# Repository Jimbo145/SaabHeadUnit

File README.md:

# SaabHeadUnit
The goal of this project is to create an alternate head unit option for the 
## saab-control

## circuit_boards

### headunit_controls

Emulates slimmed down ICM button pcb

### headunit_hub

Integrates Ibus and LCD connections to Cat V cables for routing out of ICM

### headunit_pi4

Pi4 mounting, Lifepowered, Microphone module, power input

# Project Phases

## Phase 1 -- ICM2 Integration

Parts list
[Raspberry Pi LCD 3.5inch touchscreen 480*800 capacitive](https://www.aliexpress.us/item/3256802078662650.html)
[lifepo4wered-pi+](https://lifepo4wered.com/lifepo4wered-pi+.html)
[Can Bus Module Mcp2515](https://www.aliexpress.us/item/3256802493611620.html)

## Phase 2 -- ICM Frontend Replacement

# Acknowledgement 

[leighleighleigh](https://github.com/leighleighleigh)
[Patrick Van Oosterwijck and LiFePO4wered](https://lifepo4wered.com)
[Trionic Tuning](https://www.trionictuning.com/forum/viewtopic.php?f=46&t=8566)

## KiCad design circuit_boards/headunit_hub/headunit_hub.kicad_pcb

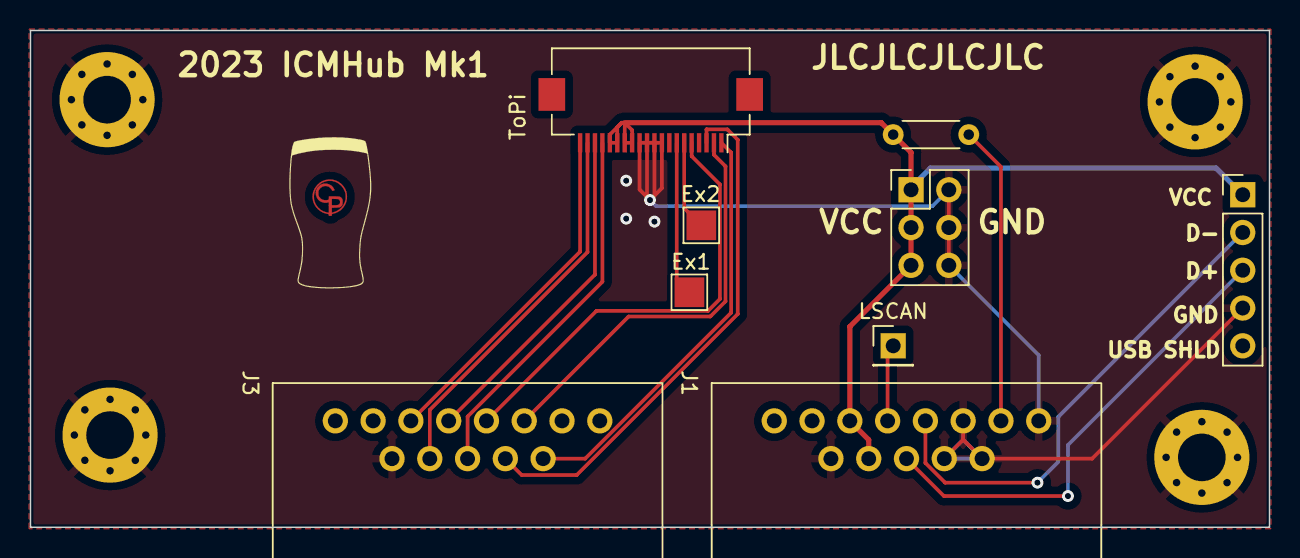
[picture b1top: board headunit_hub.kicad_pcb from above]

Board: 2 copper layers, 83.3 x 33.4 mm, 14 parts (0 on the bottom side), 16 nets.

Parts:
Ex1, Ex2: Conn_01x01_Pin; TestPoint_Pad_2.0x2.0mm
H1, H2, H4, H5: MountingHole_Pad; MountingHole_3.2mm_M3_Pad_Via
H3: Logo; CPlogo2(50)
J1, J3: 8P8C_LED_Shielded; rj45breakout
J5: USB_A; PinHeader_1x05_P2.54mm_Vertical
J6: Conn_02x03_Odd_Even; PinHeader_2x03_P2.54mm_Vertical
LSCAN: LSCAN; PinHeader_1x01_P2.54mm_Vertical
R1: R; R_Axial_DIN0204_L3.6mm_D1.6mm_P5.08mm_Horizontal
ToPi: Conn_01x20; Hirose_FH12-20S-0.5SH_1x20-1MP_P0.50mm_Horizontal

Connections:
/LSCAN: J1.6, LSCAN.1
/R_to_ActiveLED: J1.10, R1.2
AMFM_button: J3.1, ToPi.1
CD_button: J3.3, ToPi.3
Expansion_4: J3.8, ToPi.20
Expansion_5: J3.7, ToPi.19
Expansion_6: J3.6, ToPi.18
Expansion_7: J3.5, ToPi.17
GND: H1.1, H2.1, H4.1, H5.1, J1.1, J1.2, J1.3, J1.9, J1.SH, J3.SH, J5.4 (GND), J6.2, J6.4, J6.6, ToPi.9, ToPi.10, ToPi.11, ToPi.12
unnamed: Ex1.1, ToPi.7
unnamed: Ex2.1, ToPi.6
unnamed: J1.5, J5.3 (D+)
unnamed: J1.4, J5.2 (D-)
SCAN_button: J3.2, ToPi.2
Scrn_Brightness: J3.4, ToPi.5
VCC: J1.7, J1.8, J5.1 (VBUS), J6.1, J6.3, J6.5, R1.1, ToPi.13, ToPi.14, ToPi.15, ToPi.16

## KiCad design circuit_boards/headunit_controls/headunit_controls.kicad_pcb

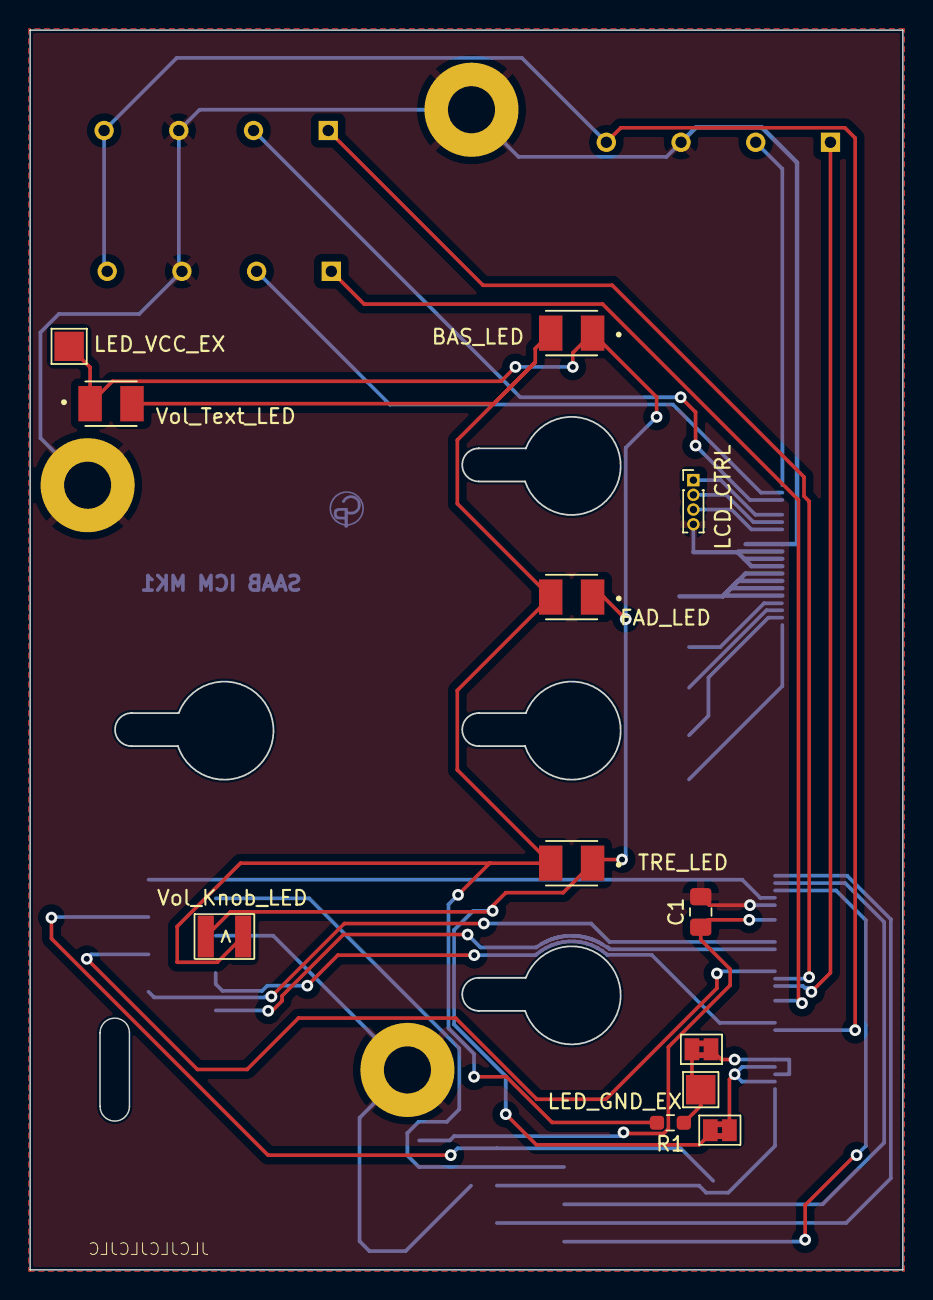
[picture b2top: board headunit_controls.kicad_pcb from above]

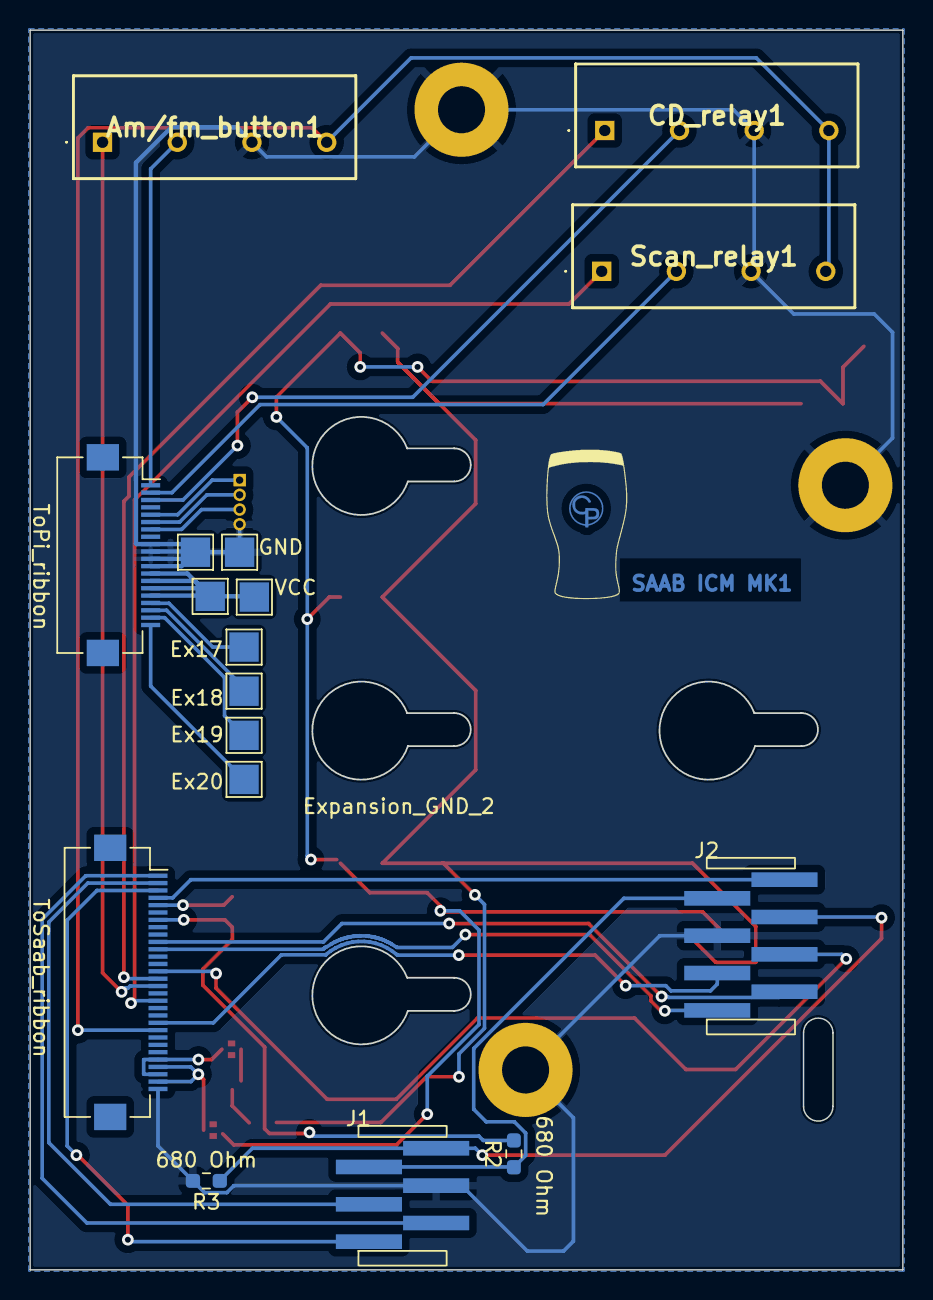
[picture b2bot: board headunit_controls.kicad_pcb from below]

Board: 2 copper layers, 59.3 x 84.3 mm, 37 parts (18 on the bottom side), 32 nets.

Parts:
Am/fm_button1: SIP-1A05; SIP1A05
BAS_LED: LED_Small; LED_OF-SMD3528WC
BTR_1, BTR_2, BTR_3: MountingHole_Pad; SaabBTR
C1: C; C_0805_2012Metric_Pad1.18x1.45mm_HandSolder
CD_relay1: SIP-1A05; SIP1A05
Ex17, Ex18, Ex19, Ex20: Conn_01x01_Pin; TestPoint_Pad_2.0x2.0mm
Expansion_GND_2: Conn_01x01_Pin; TestPoint_Pad_2.0x2.0mm
Expansion_VCC_2: Conn_01x01_Pin; TestPoint_Pad_2.0x2.0mm
FAD_LED: LED_Small; LED_OF-SMD3528WC
GND: Conn_01x01_Pin; TestPoint_Pad_2.0x2.0mm
J1: Conn_01x06; SaabConnector_6
J2: Conn_01x08; SaabConnector_8
JP1, JP2: SolderJumper_2_Bridged; SolderJumper-2_P1.3mm_Bridged2Bar_Pad1.0x1.5mm
LCD_CTRL: Conn_01x04_Pin; PinHeader_1x04_P1.00mm_Vertical
LED_GND_EX: Conn_01x01_Pin; TestPoint_Pad_2.0x2.0mm
LED_VCC_EX: Conn_01x01_Pin; TestPoint_Pad_2.0x2.0mm
M3_1, M3_2, M3_3: MountingHole_Pad; MountingHole_3.2mm_M3_Pad
R1: R; R_0603_1608Metric_Pad0.98x0.95mm_HandSolder
R2, R3: 680 Ohm; R_0603_1608Metric_Pad0.98x0.95mm_HandSolder
Ref**: Val**; CPlogo2(50)
Scan_relay1: SIP-1A05; SIP1A05
TRE_LED: LED_Small; LED_OF-SMD3528WC
ToPi_ribbon: Conn_01x20; Hirose_FH12-20S-0.5SH_1x20-1MP_P0.50mm_Horizontal
ToSaab_ribbon: Conn_01x30; Hirose_FH12-30S-0.5SH_1x30-1MP_P0.50mm_Horizontal
VCC: Conn_01x01_Pin; TestPoint_Pad_2.0x2.0mm
VOL_1: MountingHole_Pad; SaabBTR
Vol_Knob_LED: LED_Small; Songxin_1210_side
Vol_Text_LED: LED_Small; LED_OF-SMD3528WC

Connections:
15: CD_relay1.1 (Contact_A), ToSaab_ribbon.15
16: Am/fm_button1.1 (Contact_A), ToSaab_ribbon.16
18: Scan_relay1.1 (Contact_A), ToSaab_ribbon.18
22: Am/fm_button1.4 (Contact_B), CD_relay1.4 (Contact_B), Scan_relay1.4 (Contact_B), ToSaab_ribbon.22
/SCREEN_CLK: LCD_CTRL.2, ToPi_ribbon.6
/SCREEN_DIO: LCD_CTRL.3, ToPi_ribbon.7
/SCREEN_RST: LCD_CTRL.1, ToPi_ribbon.5
AMFM_button: Am/fm_button1.2 (Coil_A), ToPi_ribbon.1
BAS: J1.3, ToSaab_ribbon.2
BTFR_BALL_CON: C1.1, R2.2, ToSaab_ribbon.7
Bal_Center: J2.8, ToSaab_ribbon.4
CD_button: CD_relay1.2 (Coil_A), ToPi_ribbon.3
FAD: J1.2, ToSaab_ribbon.1
GND: Am/fm_button1.3 (Coil_B), C1.2, CD_relay1.3 (Coil_B), Expansion_GND_2.1, GND.1, J1.4, J2.5, LCD_CTRL.4, M3_1.1, M3_2.1, M3_3.1, R3.2, Scan_relay1.3 (Coil_B), ToPi_ribbon.9, ToPi_ribbon.10, ToPi_ribbon.11, ToPi_ribbon.12, ToSaab_ribbon.5, ToSaab_ribbon.9, ToSaab_ribbon.30
LED_Feed: JP1.1 (A), ToSaab_ribbon.26, ToSaab_ribbon.28
LED_GND: JP2.2 (B), ToSaab_ribbon.27, ToSaab_ribbon.29
unnamed: BAS_LED.2 (A), FAD_LED.2 (A), R1.2, TRE_LED.2 (A), Vol_Knob_LED.2 (A), Vol_Text_LED.2 (A)
unnamed: BAS_LED.1 (K), FAD_LED.1 (K), JP2.1 (A), LED_VCC_EX.1, TRE_LED.1 (K), Vol_Knob_LED.1 (K), Vol_Text_LED.1 (K)
unnamed: Ex17.1, ToPi_ribbon.17
unnamed: Ex18.1, ToPi_ribbon.18
unnamed: Ex19.1, ToPi_ribbon.19
unnamed: Ex20.1, ToPi_ribbon.20
unnamed: JP1.2 (B), LED_GND_EX.1, R1.1
unnamed: J1.5, J2.7, R2.1
unnamed: J1.6, J2.6, R3.1
unnamed: J2.4, ToSaab_ribbon.14
SCAN_button: Scan_relay1.2 (Coil_A), ToPi_ribbon.2
TRE: J1.1, ToSaab_ribbon.3
VCC: Expansion_VCC_2.1, ToPi_ribbon.13, ToPi_ribbon.14, ToPi_ribbon.15, ToPi_ribbon.16, VCC.1
Vol_buttonB: J2.3, ToSaab_ribbon.21
Vol_encA: J2.2, ToSaab_ribbon.10
Vol_encB: J2.1, ToSaab_ribbon.11

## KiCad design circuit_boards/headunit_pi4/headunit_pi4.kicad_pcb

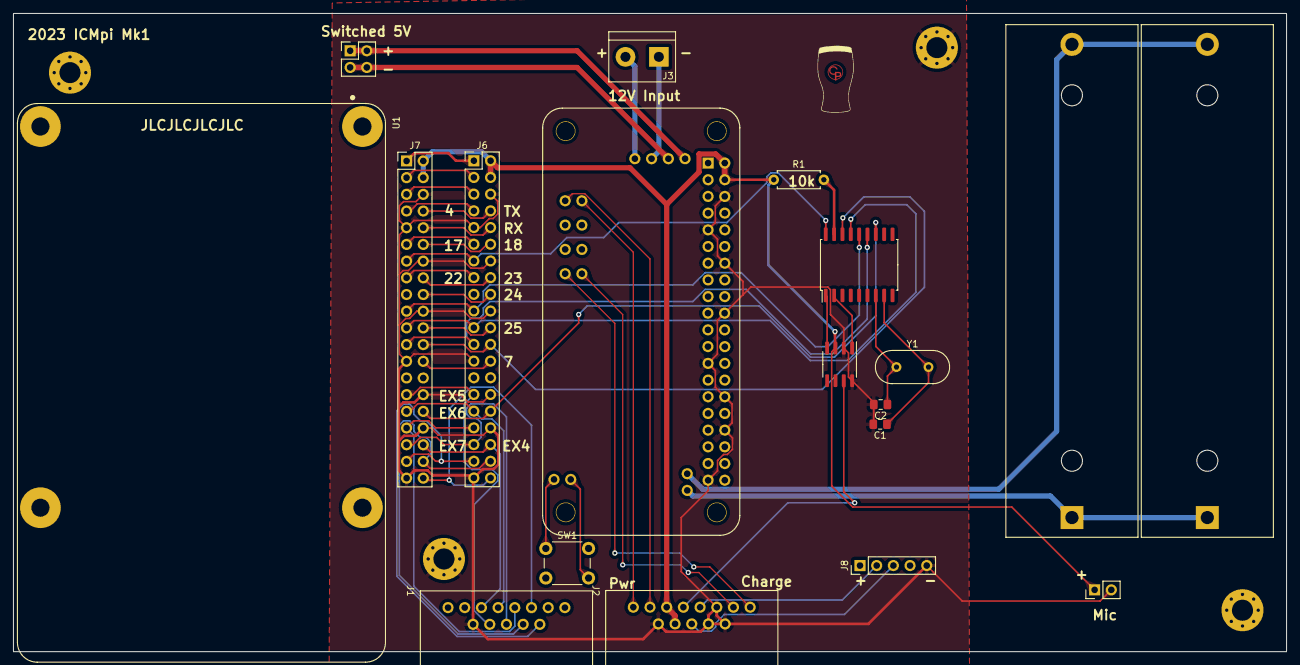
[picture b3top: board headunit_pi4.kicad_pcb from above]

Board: 2 copper layers, 193.7 x 97.1 mm, 24 parts (0 on the bottom side), 50 nets.

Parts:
BT1, BT2: Battery_Cell; BatteryHolder_MPD_BH-18650-PC2
C1, C2: 22p; C_0805_2012Metric_Pad1.18x1.45mm_HandSolder
H1, H2, H3, H4: MountingHole_Pad; MountingHole_3.2mm_M3_Pad_Via
H5: MountingHole; CPlogo2(50)
J1, J2: 8P8C_LED_Shielded; rj45breakout
J3: Screw_Terminal_01x02; TerminalBlock_bornier-2_P5.08mm
J4: Conn_01x02; PinHeader_1x02_P2.54mm_Vertical
J5: Conn_02x02_Counter_Clockwise; PinHeader_2x02_P2.54mm_Vertical
J6, J7: Conn_02x20_Odd_Even; PinHeader_2x20_P2.54mm_Vertical
J8: USB_B_Mini; PinHeader_1x05_P2.54mm_Vertical
R1: 10k; R_Axial_DIN0207_L6.3mm_D2.5mm_P7.62mm_Horizontal
SW1: SW_Push; SW_PUSH_6mm
U1: RASPBERRY_PI_4B_4GB; MODULE_RASPBERRY_PI_4B_4GB_NOPIN
U2: TJA1051T; SOIC-8_3.9x4.9mm_P1.27mm
U3: MCP2515-xSO; SOIC-18W_7.5x11.6mm_P1.27mm
U4: LiFoPower
Y1: 8Mhz; Crystal_HC49-U_Vertical

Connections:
+3.3V: J6.1, J7.1
AMFM_button: J1.1, J6.37, J7.37
CAN_INT: J6.32, J7.32, U3.12 (~INT)
CD_button: J1.3, J6.38, J7.38
ChargeLED+: J2.10, U4.Cled+ (ChargeLED+)
ChargeLED-: J2.9, U4.Cled- (ChargeLED-)
Expansion_4: J1.8, J6.36, J7.36
Expansion_5: J1.7, J6.29, J7.29
Expansion_6: J1.6, J6.31, J7.31
Expansion_7: J1.5, J6.35, J7.35
GND: C1.2, C2.2, H1.1, H2.1, H3.1, H4.1, J1.SH, J2.1, J2.2, J2.3, J2.SH, J4.2, J6.6, J6.9, J6.14, J6.20, J6.25, J6.30, J6.34, J6.39, J7.6, J7.9, J7.14, J7.20, J7.25, J7.30, J7.34, J7.39, J8.5 (GND), U2.2 (GND), U2.8 (S), U4.6 (GND), U4.9 (GND), U4.14 (GND), U4.20 (GND), U4.25 (GND), U4.30 (GND), U4.34 (GND), U4.39 (GND)
GPIO4: J6.7, J7.7
GPIO7: J6.26, J7.26
GPIO17: J6.11, J7.11
GPIO18: J6.12, J7.12
GPIO22: J6.15, J7.15
GPIO23: J6.16, J7.16
GPIO24: J6.18, J7.18
GPIO25: J6.22, J7.22
LSCAN: J2.6, U2.7 (CANH)
MCP_PWR: J6.13, J7.13, U3.18 (VDD)
unnamed: BT1.1 (+), BT2.1 (+), U4.B+ (Bat+)
unnamed: BT1.2 (-), BT2.2 (-), U4.B- (Bat-)
unnamed: J3.1, U4.Vcar- (12VGND)
unnamed: J3.2, U4.Vcar+ (12V+)
unnamed: J5.1, J5.2, U4.Vout+
unnamed: J5.3, J5.4, U4.Vout-
unnamed: J2.5, J8.3 (D+)
unnamed: J2.4, J8.2 (D-)
unnamed: U1.S1 (SHIELD), U1.S2 (SHIELD), U1.S3 (SHIELD), U1.S4 (SHIELD)
unnamed: U2.4 (RXD), U3.1 (TXCAN)
unnamed: U2.1 (TXD), U3.2 (RXCAN)
unnamed: C1.1, U3.8 (OSC1), Y1.2
unnamed: C2.1, U3.7 (OSC2), Y1.1
unnamed: R1.2, U3.17 (~RESET)
unnamed: SW1.2, U4.btn+ (BTN+)
unnamed: SW1.1, U4.btn- (BTN-)
PwrLED+: J2.12, U4.Pled+ (PowerLED+)
PwrLED-: J2.11, U4.Pled- (PowerLED-)
RX0: J6.10, J7.10
SCAN_button: J1.2, J6.40, J7.40
SCL1: J6.5, J7.5, U4.5 (SCL)
SDA1: J6.3, J7.3, U4.3 (SDA)
SPI0_CE0: J6.24, J7.24, U3.16 (~CS)
SPI0_MISO: J6.21, J7.21, U3.15 (SO)
SPI0_MOSI: J6.19, J7.19, U3.14 (SI)
SPI0_SCLK: J6.23, J7.23, U3.13 (SCK)
Scrn_Brightness: J1.4, J6.33, J7.33
TX0: J6.8, J7.8, U4.8 (TX0)
VCC: J2.7, J2.8, J4.1, J6.2, J6.4, J7.2, J7.4, R1.1, U2.3 (VCC), U4.2 (VCC), U4.4 (VCC)

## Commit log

2021-05-27 Initial commit native pigpio control
2021-05-27 Update Git Ignore
2021-05-30 Somewhat working SDL package
2023-01-27 Initial commit of saab-control python scripts
2023-01-30 Add installation script and service
2023-02-11 changes to name structure and python location
2023-02-15 Update file paths
2023-03-05 Update file paths add turn signal logic
2023-03-06 Add pyzmq import
2023-03-07 Change Service script location
2023-03-07 Change Service script location (#2)
2023-03-13 Remove gitpython
2023-03-13 Dev (#3)
    * Change Service script location
    * Remove gitpython
    ---------
2023-03-14 Attempt to move Fog light on and aux change to updater.
2023-03-14 Dev (#4)
    * Change Service script location
    * Remove gitpython
    * Attempt to move Fog light on and aux change to updater.
    ---------
2023-03-14 Change Updater to run in a standalone service
2023-03-14 Dev (#5)
    * Change Service script location
    * Remove gitpython
    * Attempt to move Fog light on and aux change to updater.
    * Change Updater to run in a standalone service
    * Change Updater to run in a standalone service
    ---------
2023-03-14 Modify service files so they point to right path and are executed in order
2023-03-14 Dev (#6)
    * Change Service script location
    * Remove gitpython
    * Attempt to move Fog light on and aux change to updater.
    * Change Updater to run in a standalone service
    * Change Updater to run in a standalone service
    * Modify service files so they point to right path and are executed in order
2023-03-14 Dev (#7)
    * Change Service script location
    * Remove gitpython
    * Attempt to move Fog light on and aux change to updater.
    * Change Updater to run in a standalone service
    * Change Updater to run in a standalone service
    * Modify service files so they point to right path and are executed in order
2023-03-14 modify install.sh to work if already installed. Move After key in saab.service
2023-03-14 Dev (#8)
    * Change Service script location
    * Remove gitpython
    * Attempt to move Fog light on and aux change to updater.
    * Change Updater to run in a standalone service
    * Change Updater to run in a standalone service
    * Modify service files so they point to right path and are executed in order
2023-03-14 modify radio change messages, move foglight on back to saabCan.py
2023-03-14 Dev (#9)
    * Change Service script location
    * Remove gitpython
    * Attempt to move Fog light on and aux change to updater.
    * Change Updater to run in a standalone service
    * Change Updater to run in a standalone service
    * Modify service files so they point to right path and are executed in order
2023-03-15 Change copy command to bash
2023-03-15 Dev (#10)
    * Change Service script location
    * Remove gitpython
    * Attempt to move Fog light on and aux change to updater.
    * Change Updater to run in a standalone service
    * Change Updater to run in a standalone service
    * Modify service files so they point to right path and are executed in order
2023-03-20 remove attempt at automatic radio change. change back to get pull
2023-03-20 Dev (#11)
    * Change Service script location
    * Remove gitpython
    * Attempt to move Fog light on and aux change to updater.
    * Change Updater to run in a standalone service
    * Change Updater to run in a standalone service
    * Modify service files so they point to right path and are executed in order
2023-03-21 Update to updater to only update when updates are required
2023-03-21 Update to updater to only update when updates are required (#12)
2023-03-28 import os and remove unnecessary requirements for saab.service
2023-03-28 Updater refresh (#13)
    * Update to updater to only update when updates are required
    * import os and remove unnecessary requirements for saab.service
    ---------
2023-03-31 add api (currently commented out). add journalctl logging add automatic source changing
2023-03-31 Dev (#14)
    * Change Service script location
    * Remove gitpython
    * Attempt to move Fog light on and aux change to updater.
    * Change Updater to run in a standalone service
    * Change Updater to run in a standalone service
    * Modify service files so they point to right path and are executed in order
2023-04-05 Add Async to get_battery_status and extend install.sh
2023-04-06 Dev (#15)
    * Change Service script location
    * Remove gitpython
    * Attempt to move Fog light on and aux change to updater.
    * Change Updater to run in a standalone service
    * Change Updater to run in a standalone service
    * Modify service files so they point to right path and are executed in order
2023-04-10 add requirements.txt change systemd journal handling
2023-04-10 Dev (#16)
    * Change Service script location
    * Remove gitpython
    * Attempt to move Fog light on and aux change to updater.
    * Change Updater to run in a standalone service
    * Change Updater to run in a standalone service
    * Modify service files so they point to right path and are executed in order
2023-04-12 Update updater
2023-04-12 Dev (#17)
    * Change Service script location
    * Remove gitpython
    * Attempt to move Fog light on and aux change to updater.
    * Change Updater to run in a standalone service
    * Change Updater to run in a standalone service
    * Modify service files so they point to right path and are executed in order
2023-04-12 Start updater sooner, and stop if an update is necessary.
2023-04-12 Start updater sooner, and stop if an update is necessary. (#18)
2023-04-14 Bug Fix: use systemd-python rather than systemd
2023-04-14 Bug Fix: use systemd-python rather than systemd (#19)
2023-04-14 Bug Fix: add back can configuration, add await to copy_files
2023-04-14 Bug Fix: add back can configuration, add await to copy_files (#20)
2023-04-14 Create python-app.yml (#21)
2023-04-15 Fix saab.service script path. Add absolute path to requirements.txt for installer
2023-04-15 Fix saab.service script path. Add absolute path to requirements.txt for installer (#22)
2023-04-15 logger changes, call ip link up as sudo
2023-04-15 logger changes, call ip link up as sudo (#23)
2023-04-15 fix duplicate bracket
2023-04-15 fix duplicate bracket (#24)
2023-04-15 Change saab_update to graphical.target
2023-04-15 Change saab_update to graphical.target (#25)
2023-04-16 logging changes, fix message not sending until receive
2023-04-16 Dev (#26)
    * Change saab_update to graphical.target
    * logging changes, fix message not sending until receive
    ---------
2023-04-18 Feature: Add Auto-restart to saab.service
2023-04-18 Feature: Add Auto-restart to saab.service (#27)
2023-04-22 Add wait condition for pynput to prevent saabCan from failing if Xorg is not yet available
2023-04-22 Add wait condition for pynput to prevent saabCan from failing if Xorg is not yet available (#28)
2023-04-22 Fix source change button send, change log levels
2023-04-22 Fix source change button send, change log levels (#29)
2023-04-22 Fix source change button send, change log levels (#30)
2023-04-23 Fix update check, again change logging
2023-04-23 Fix update check, again change logging (#31)
2023-04-24 Bug fix: increase source change delay Feature: Additional logging support
2023-04-24 Bug fix: increase source change delay (#32)
    Feature: Additional logging support
2023-04-25 Cleanup repo and add documentation
2023-04-25 Cleanup repo and add documentation (#33)
2023-04-25 Feature: Add Additional Can Message Support
2023-04-25 Feature: Add Additional Can Message Support (#34)
2023-04-27 Add preliminary support for more can ids. Fix NXT button support
2023-04-28 Add preliminary support for more can ids.
2023-04-28 Adjust update
2023-04-28 Adjust update (#35)
2023-04-28 BugFix: Turn signal global variables not defined until 290 message received Feature: Added 0x143 and 0x144 canid support (windshield wipers) Change: Change 0x180 and 0x183 (Parking sensor) log messag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
2023-05-01 BugFix: Turn signal global variables not defined until 290 message received (#36)
    Feature: Added 0x143 and 0x144 canid support (windshield wipers)
    Change: Change 0x180 and 0x183 (Parking sensor) log message level
2023-05-03 Bug Fix: Turn signal handle direction Bug Fix: Fix Right turn signal timer Feature: Added Update Rev to update file
2023-05-03 Bug Fix: Turn signal handle direction (#37)
    Bug Fix: Fix Right turn signal timer
    Feature: Added Update Rev to update file
2024-02-10 Modified Kicad Files
2024-02-10 BugFix: Turn signal euro flash always active
2024-02-10 Dev (#38)
    * BugFix: Turn signal global variables not defined until 290 message received
    Feature: Added 0x143 and 0x144 canid support (windshield wipers)
    Change: Change 0x180 and 0x183 (Parking sensor) log message level
    * Modified Kicad Files
    * BugFix: Turn signal euro flash always active
    ---------
2024-02-12 Dev (#39)
    * BugFix: Turn signal global variables not defined until 290 message received
    Feature: Added 0x143 and 0x144 canid support (windshield wipers)
    Change: Change 0x180 and 0x183 (Parking sensor) log message level
    * Bug Fix: Turn signal handle direction
    Bug Fix: Fix Right turn signal timer
    Feature: Added Update Rev to update file
2024-02-13 Bug Fix: intialize Keypressed Bug Fix: turn sigal last state fix
2024-02-13 Dev (#40)
    * BugFix: Turn signal global variables not defined until 290 message received
    Feature: Added 0x143 and 0x144 canid support (windshield wipers)
    Change: Change 0x180 and 0x183 (Parking sensor) log message level
    * Bug Fix: Turn signal handle direction
    Bug Fix: Fix Right turn signal timer
    Feature: Added Update Rev to update file
2024-02-13 Bug Fix: Expose debugging website to wlan
2024-02-13 Dev (#41)
    * Bug Fix: Expose debugging website to wlan
    ---------
2024-06-21 Add devcontainer
2024-06-21 Add gitattributes
2024-06-21 Add dockerfile back
2024-06-21 Try to fix line-endings
2024-06-21 Git attributes
2024-07-26 Add webserver and improve testing capability
2024-08-05 add libs ciruit_boards
2024-08-22 Add webserver logic with websocket connection
